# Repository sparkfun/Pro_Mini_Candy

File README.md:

**NOTE:** *This product has been retired from our catalog as this was for a special promotion. If you are looking for more up-to-date info, please check out some of these resources to see how other users are still hacking, improving, and using on this product with the [Arduino Pro Mini 5V/16MHz](https://www.sparkfun.com/products/11113).*
* *[SparkFun Forum](https://forum.sparkfun.com/)*
* *[IRC Channel](https://www.sparkfun.com/news/263)*

SparkFun Pro Mini Candy
===============

[*SparkFun  Pro Mini Candy (DEV-12627)*](https://www.sparkfun.com/products/retired/12627)

This is a repository for the special SparkFun version of the Arduino Pro Mini 5V/16 MHz board.

It is designed to be used as a complimentary board to send out with holiday orders. Check out the special regarding this [here](https://www.sparkfun.com/news/1334).

Repository Contents
-------------------

* **/Firmware** - Example code 
* **/Hardware** - Eagle design files (.brd, .sch)
* **/Production** - Production panel files (.brd)

Documentation
--------------

* **[Hookup Guide](https://learn.sparkfun.com/tutorials/using-the-arduino-pro-mini-33v)** - Basic hookup guide for the Arduino Pro Mini 3.3V/8MHz. It can be used as a guide with the 5V. The only difference when following the tutorial is selecting the board definition in the Arduino IDE and the voltage levels.
* **[Limited Edition Christmas Candy Pro Mini](https://www.sparkfun.com/news/1334)** - Blog post about the special Pro Mini Candy.

License Information
-------------------

This product is _**open source**_! 

Please review the LICENSE.md file for license information. 

If you have any questions or concerns on licensing, please contact techsupport@sparkfun.com.

Distributed as-is; no warranty is given.

- Your friends at SparkFun.

_<COLLABORATION CREDIT>_

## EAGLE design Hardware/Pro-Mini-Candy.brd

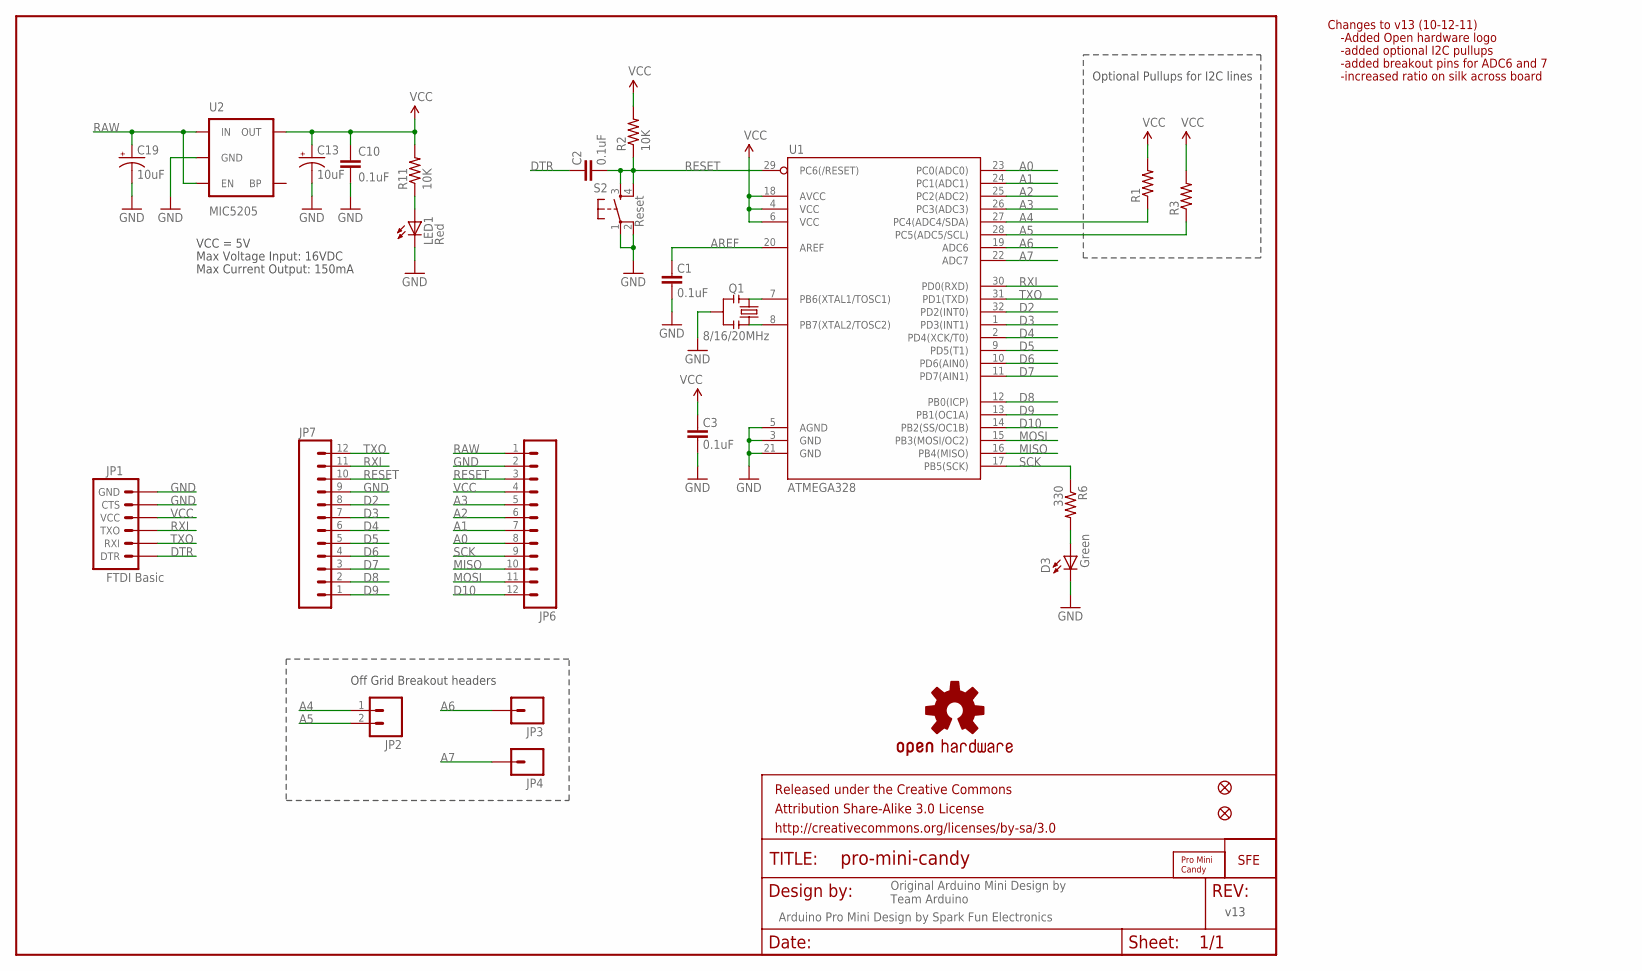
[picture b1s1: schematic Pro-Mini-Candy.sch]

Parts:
C1, C2, C3, C10: 0.1uF; 0402-CAP
C13, C19: 10uF; EIA3216
D3: Green; LED-0603
FRAME1: FRAME-LETTER; CREATIVE_COMMONS
JP1: FTDI Basic; 1X06
JP2: M02PTH; 1X02
JP3, JP4: M01PTH; 1X01
JP5, JP8: FIDUCIALUFIDUCIAL; MICRO-FIDUCIAL
JP6, JP7: M12PTH; 1X12
LED1: Red; LED-0603
Q1: 8/16/20MHz; RESONATOR-SMD
R1, R3: RESISTOR0402-RES; 0402-RES
R2, R11: 10K; 0402-RES
R6: 330; 0402-RES
S2: Reset; TACTILE_SWITCH_SMD
U1: ATMEGA328; TQFP32-08
U2: MIC5205; SOT23-5
U$1: LOGO-SFESK; SFE-LOGO-FLAME
U$2: PRO_MINI_CANDY
U$3: OSHW-LOGOS; OSHW-LOGO-S

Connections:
A0: JP6.8, U1.23 (PC0(ADC0))
A1: JP6.7, U1.24 (PC1(ADC1))
A2: JP6.6, U1.25 (PC2(ADC2))
A3: JP6.5, U1.26 (PC3(ADC3))
A4: JP2.1, R1.1, U1.27 (PC4(ADC4/SDA))
A5: JP2.2, R3.1, U1.28 (PC5(ADC5/SCL))
A6: JP3.1, U1.19 (ADC6)
A7: JP4.1, U1.22 (ADC7)
AREF: C1.2, U1.20 (AREF)
D2: JP7.8, U1.32 (PD2(INT0))
D3: JP7.7, U1.1 (PD3(INT1))
D4: JP7.6, U1.2 (PD4(XCK/T0))
D5: JP7.5, U1.9 (PD5(T1))
D6: JP7.4, U1.10 (PD6(AIN0))
D7: JP7.3, U1.11 (PD7(AIN1))
D8: JP7.2, U1.12 (PB0(ICP))
D9: JP7.1, U1.13 (PB1(OC1A))
D10: JP6.12, U1.14 (PB2(SS/OC1B))
DTR: C2.2, JP1.1 (DTR)
GND: C1.1, C3.1, C10.2, C13.C (-), C19.C (-), D3.C, JP1.5 (CTS), JP1.6 (GND), JP6.2, JP7.9, LED1.C, Q1.2, S2.1, S2.2, U1.3 (GND), U1.5 (AGND), U1.21 (GND), U2.2 (GND)
MISO: JP6.10, U1.16 (PB4(MISO))
MOSI: JP6.11, U1.15 (PB3(MOSI/OC2))
unnamed: Q1.1, U1.8 (PB7(XTAL2/TOSC2))
unnamed: Q1.3, U1.7 (PB6(XTAL1/TOSC1))
unnamed: D3.A, R6.2
unnamed: LED1.A, R11.1
RAW: C19.A (+), JP6.1, U2.1 (IN), U2.3 (EN)
RESET: C2.1, JP6.3, JP7.10, R2.1, S2.3, S2.4, U1.29 (PC6(/RESET))
RXI: JP1.3 (TXO), JP7.11, U1.30 (PD0(RXD))
SCK: JP6.9, R6.1, U1.17 (PB5(SCK))
TXO: JP1.2 (RXI), JP7.12, U1.31 (PD1(TXD))
VCC: C3.2, C10.1, C13.A (+), JP1.4 (VCC), JP6.4, R1.2, R2.2, R3.2, R11.2, U1.4 (VCC), U1.6 (VCC), U1.18 (AVCC), U2.5 (OUT)

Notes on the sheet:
Original Arduino Mini Design by Team Arduino
Arduino Pro Mini Design by Spark Fun Electronics
Max Voltage Input: 16VDC
Max Current Output: 150mA
VCC = 5V
Optional Pullups for I2C lines
Off Grid Breakout headers
Changes to v13 (10-12-11)
-Added Open hardware logo
-added optional I2C pullups
-added breakout pins for ADC6 and 7
-increased ratio on silk across board
v13

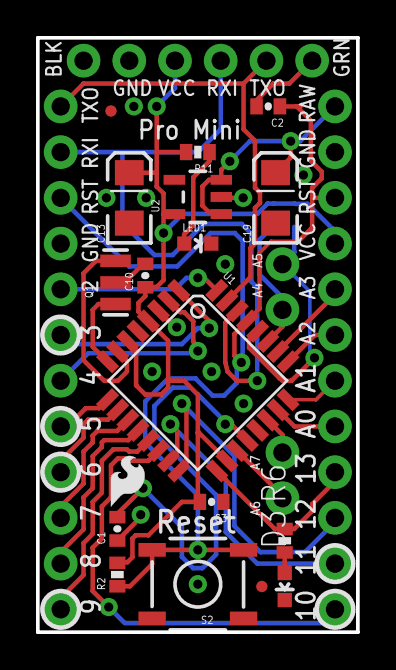
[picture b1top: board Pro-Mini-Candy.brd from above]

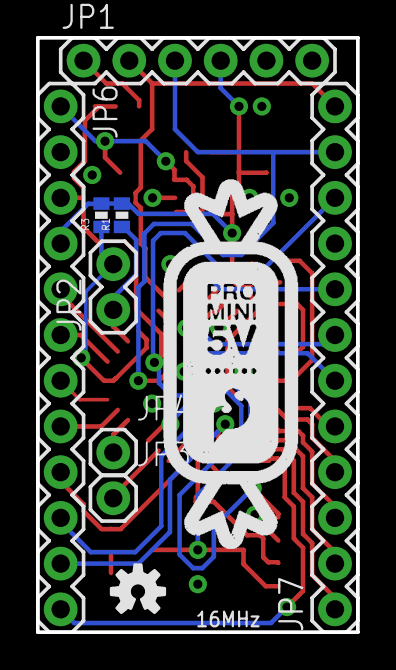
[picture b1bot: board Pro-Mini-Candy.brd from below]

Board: 2 copper layers, 17.8 x 33.0 mm, 29 parts (10 on the bottom side), 32 nets.

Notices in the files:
parts and their libraries:
SparkFun-Aesthetics: Licensing: CC v3.0 Share-Alike You are welcome to use this library for commercial purposes.
SparkFun-Aesthetics: Released under the Creative Commons Attribution Share-Alike 3.0 License
SparkFun-Aesthetics: http://creativecommons.org/licenses/by-sa/3.0
